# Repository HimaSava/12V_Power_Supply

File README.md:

# 12V_Power_Supply

A simple AC-DC 12V Power Supply.

Needed a +12V and -12V power supply for my ECG project. Didnt find a cheap alternative and I didn't want be relient only on benchtop power supplies. So made one.

ECG Project:
https://github.com/HimaSava/Single_Lead_ECG_Machine

It is a simple 2-Layer board with a 220V to 15V (500mA) centre tapped transformer. A bridge rectifier followed by a few capacitors and 7812 & 7912 voltage regulators. 

Note: Dont use a 12V transformer. There is some voltage drop in the voltage rectifiers. With a 12V transformer the output voltage is 11.75V without load. Also there is no need for heat sinks as the regulators dont get very hot due to the low current.

PCB Layout:

Assembled Circuit:

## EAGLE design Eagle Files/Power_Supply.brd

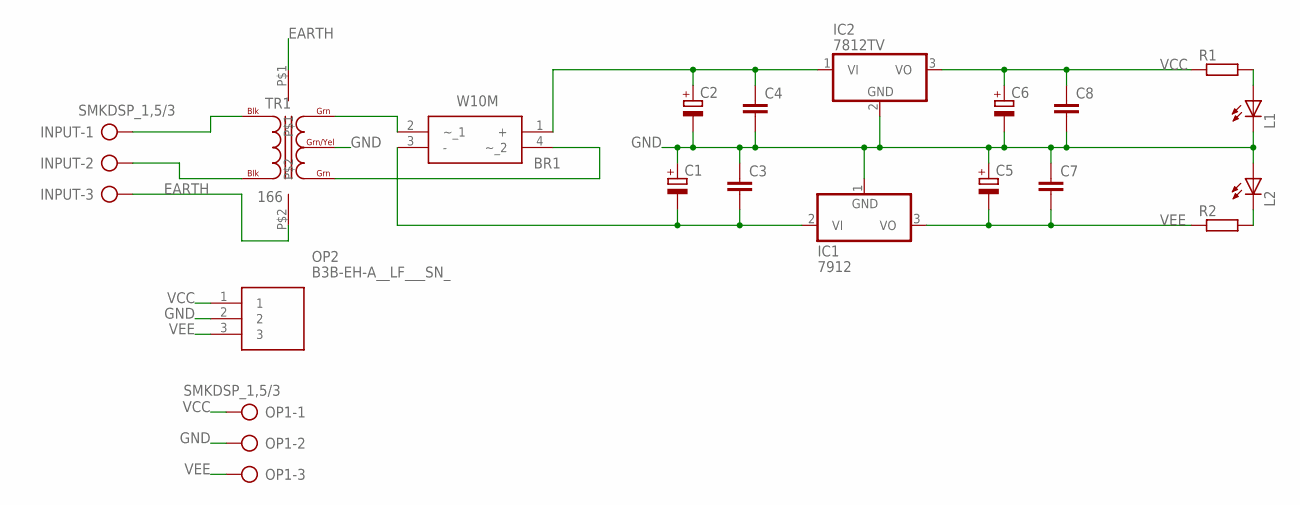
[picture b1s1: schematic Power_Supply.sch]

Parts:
BR1: W10M; WOM
C1, C2: CPOL-EUE5-10.5; E5-10,5
C3, C4, C7, C8: C-EU025-025X050; C025-025X050
C5, C6: CPOL-EUE2.5-5; E2,5-5
IC1: 7912; TO220V
IC2: 7812TV; TO220V
INPUT: SMKDSP_1,5/3
L1, L2: LED3MM
OP1: SMKDSP_1,5/3
OP2: B3B-EH-A__LF___SN_; SHDR3W64P0X250_1X3_1000X380X60
R1, R2: R-EU_0207/10; 0207/10
TR1: 166; C4H

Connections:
EARTH: INPUT.3, TR1.P$1, TR1.P$2
GND: C1.+, C2.-, C3.1, C4.2, C5.+, C6.-, C7.1, C8.2, IC1.1 (GND), IC2.2 (GND), L1.K (C), L2.A, OP1.2, OP2.2, TR1.GRN/YEL
unnamed: INPUT.1, TR1.BLK@1 (BLK)
unnamed: INPUT.2, TR1.BLK@2 (BLK)
unnamed: BR1.2 (~_1), TR1.GRN@1 (GRN)
unnamed: BR1.4 (~_2), TR1.GRN@2 (GRN)
unnamed: BR1.1 (+), C2.+, C4.1, IC2.1 (VI)
unnamed: BR1.3 (-), C1.-, C3.2, IC1.2 (VI)
unnamed: L2.K (C), R2.2
unnamed: L1.A, R1.2
VCC: C6.+, C8.1, IC2.3 (VO), OP1.1, OP2.1, R1.1
VEE: C5.-, C7.2, IC1.3 (VO), OP1.3, OP2.3, R2.1

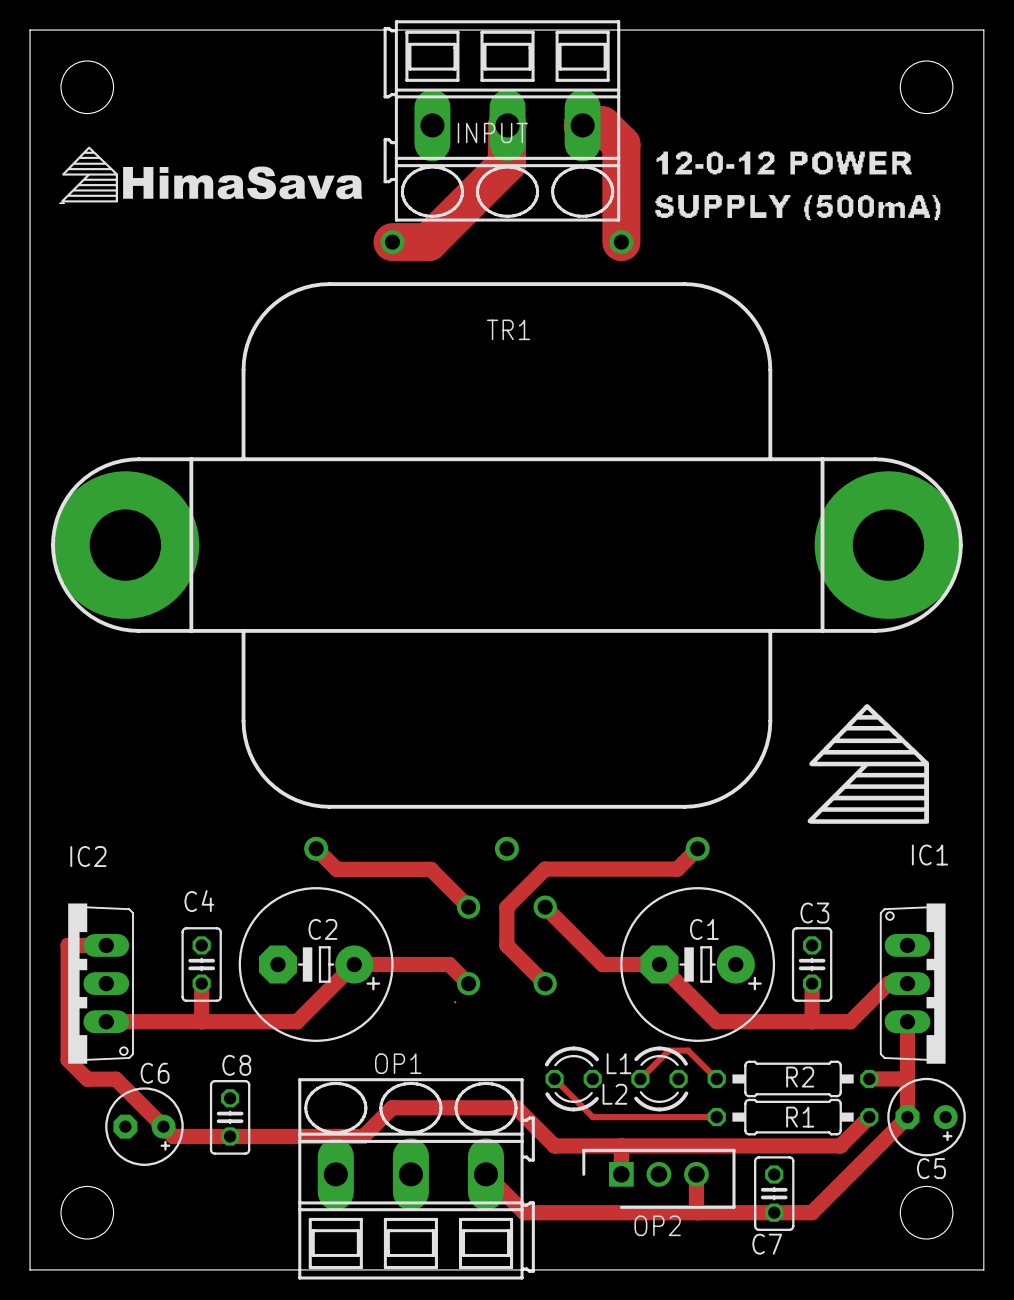
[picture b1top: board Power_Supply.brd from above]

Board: 2 copper layers, 63.5 x 82.5 mm, 19 parts (0 on the bottom side), 12 nets.

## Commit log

2021-04-21 Uploading V1 files
